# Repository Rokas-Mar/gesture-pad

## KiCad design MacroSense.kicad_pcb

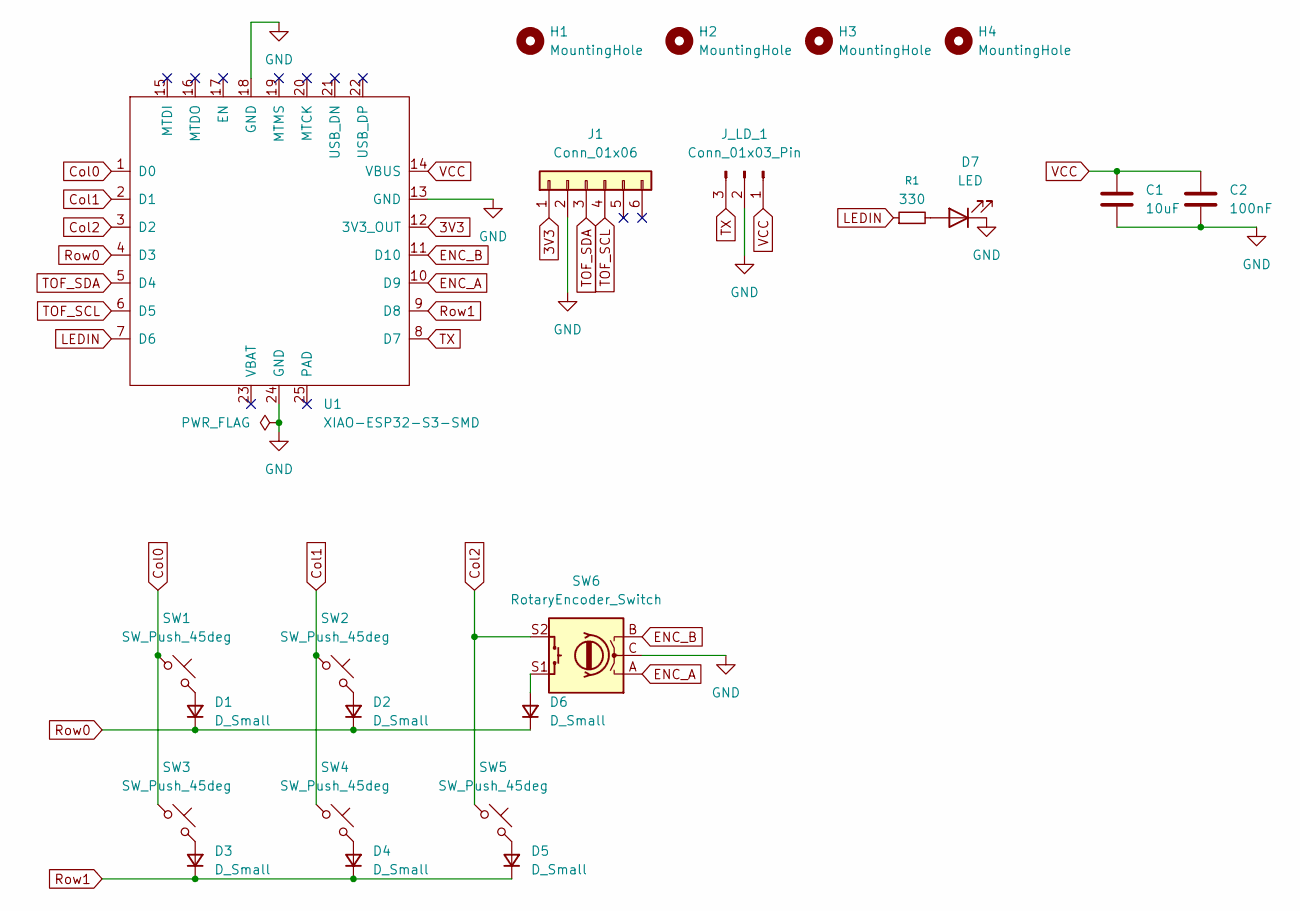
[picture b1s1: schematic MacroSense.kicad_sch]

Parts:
C1: 10uF; C_0603_1608Metric
C2: 100nF; C_0603_1608Metric
D1, D2, D3, D4, D5, D6: D_Small; D_SOD-123
D7: LED; LED_0603_1608Metric
H1, H2, H3, H4: MountingHole; MountingHole_4.3mm_M4
J1: Conn_01x06; PinHeader_1x06_P2.54mm_Vertical
J_LD_1: Conn_01x03_Pin; PinHeader_1x03_P2.54mm_Vertical
R1: 330; R_0603_1608Metric
SW1, SW2, SW3, SW4, SW5: SW_Push_45deg; SW_MX_HS_CPG151101S11_1u
SW6: RotaryEncoder_Switch; RotaryEncoder_Alps_EC11E-Switch_Vertical_H20mm
U1: XIAO-ESP32-S3-SMD

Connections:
3V3: J1.1, U1.12 (3V3_OUT)
Col0: SW1.1, SW3.1, U1.1 (D0)
Col1: SW2.1, SW4.1, U1.2 (D1)
Col2: SW5.1, SW6.S2, U1.3 (D2)
ENC_A: SW6.A, U1.10 (D9)
ENC_B: SW6.B, U1.11 (D10)
GND: C1.2, C2.2, D7.1 (K), J1.2, J_LD_1.2, SW6.C, U1.13 (GND), U1.18 (GND), U1.24 (GND)
LEDIN: R1.1, U1.7 (D6)
unnamed: D1.2 (A), SW1.2
unnamed: D2.2 (A), SW2.2
unnamed: D3.2 (A), SW3.2
unnamed: D4.2 (A), SW4.2
unnamed: D5.2 (A), SW5.2
unnamed: D6.2 (A), SW6.S1
unnamed: D7.2 (A), R1.2
Row0: D1.1 (K), D2.1 (K), D6.1 (K), U1.4 (D3)
Row1: D3.1 (K), D4.1 (K), D5.1 (K), U1.9 (D8)
TOF_SCL: J1.4, U1.6 (D5)
TOF_SDA: J1.3, U1.5 (D4)
TX: J_LD_1.3, U1.8 (D7)
VCC: C1.1, C2.1, J_LD_1.1, U1.14 (VBUS)

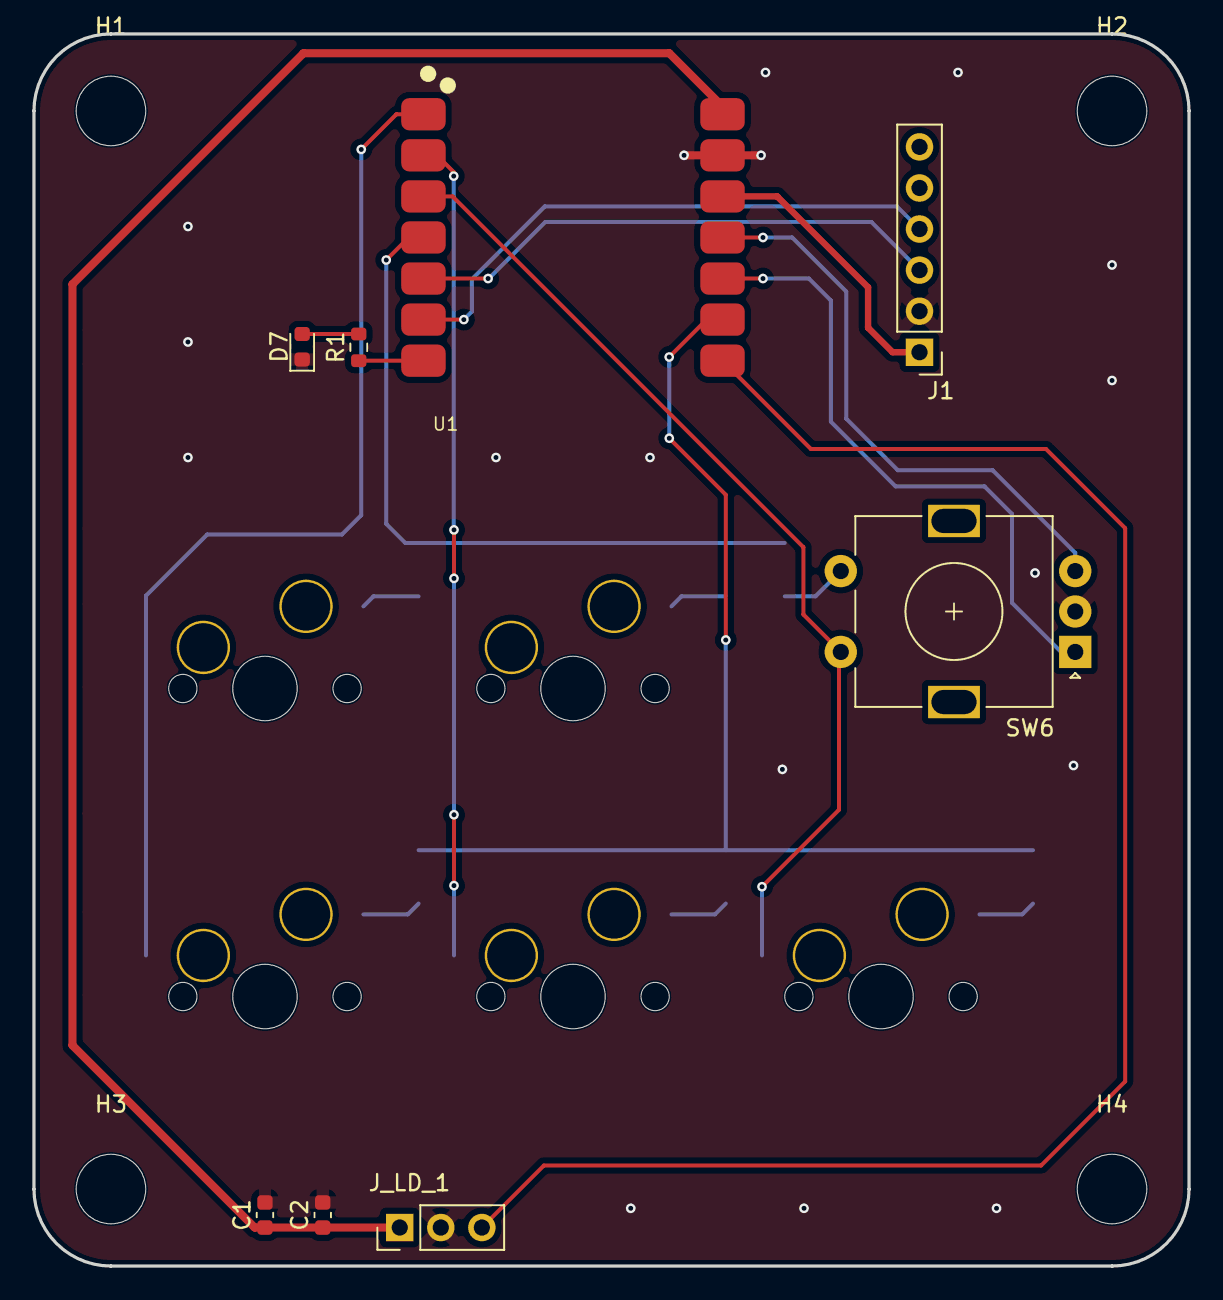
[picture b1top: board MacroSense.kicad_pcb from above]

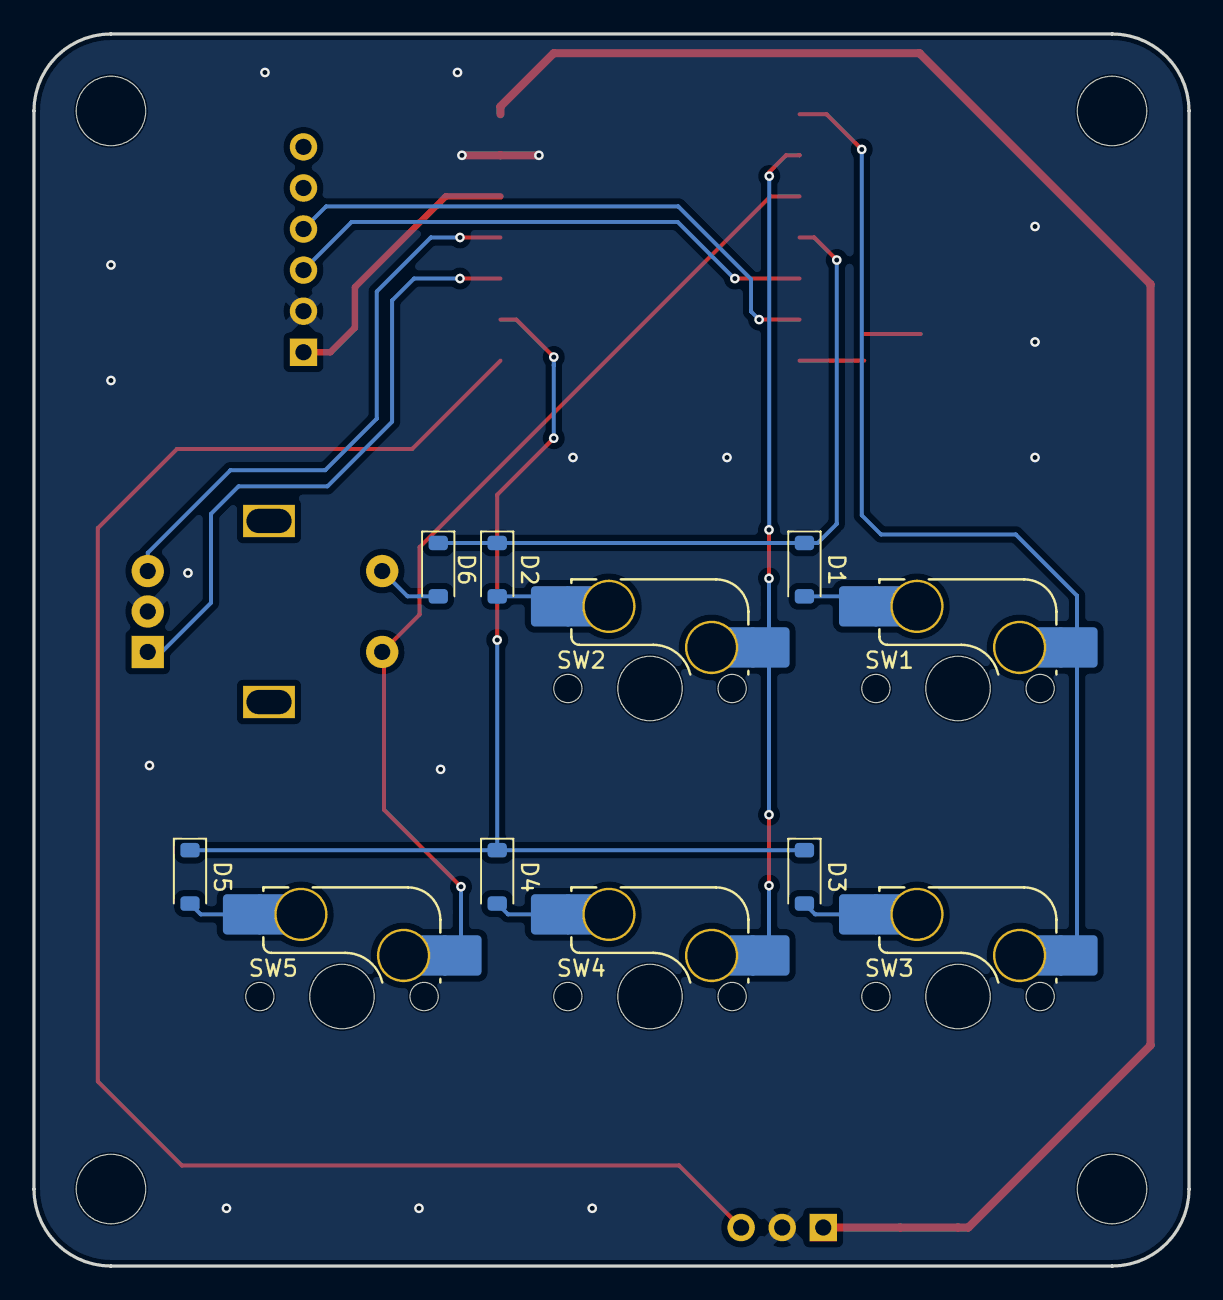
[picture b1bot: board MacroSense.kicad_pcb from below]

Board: 2 copper layers, 71.4 x 76.2 mm, 23 parts (11 on the bottom side), 21 nets.

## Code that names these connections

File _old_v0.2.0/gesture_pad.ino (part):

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// ============ PINS (from the KiCad schematic) ============
// Diodes: anode on the switch/column side, cathode on the row -> rows are driven LOW
// one at a time and columns are read with pull-ups.
static const uint8_t ROW_PINS[2] = {D3, D8};       // Row0, Row1
static const uint8_t COL_PINS[3] = {D0, D1, D2};   // Col0, Col1, Col2
#define ENC_A_PIN   D9
#define ENC_B_PIN   D10
#define LED_PIN     D6
#define TOF_SDA     D4
#define TOF_SCL     D5
// D7 (GPIO44) reserved for LD2410B TX later.

// Set to 0 if your Pololu VL53L1X library is too old to have setROISize()
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
static void pollEncoder() {
  static const int8_t table[16] = {0, -1, 1, 0, 1, 0, 0, -1, -1, 0, 0, 1, 0, 1, -1, 0};
  uint8_t s = (digitalRead(ENC_A_PIN) << 1) | digitalRead(ENC_B_PIN);
  encPrev = ((encPrev << 2) | s) & 0x0F;
  encAcc += table[encPrev];
  int steps = cfg.tune.encSteps;
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  digitalWrite(LED_PIN, HIGH);
  for (auto p : ROW_PINS) { pinMode(p, OUTPUT); digitalWrite(p, HIGH); }
  for (auto p : COL_PINS) pinMode(p, INPUT_PULLUP);
  pinMode(ENC_A_PIN, INPUT_PULLUP);
  pinMode(ENC_B_PIN, INPUT_PULLUP);

  linkMtx = xSemaphoreCreateMutex();
  inputQ = xQueueCreate(32, sizeof(InputEvt));
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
